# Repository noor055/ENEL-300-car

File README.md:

Link to Google drive: https://drive.google.com/drive/folders/1bgd8d79ywg4B1fOypwKYHgEbFJ_l1BKS?usp=sharing

Project Details:
Construct a RC car that will accomplish the following tasks:
1. Distance Sensing
2. Metal detecting
3. Design is more speed oriented

Contributers: Noor Sheikh, Ethan Lee, Youssef Salem, Ibrahim Khalid

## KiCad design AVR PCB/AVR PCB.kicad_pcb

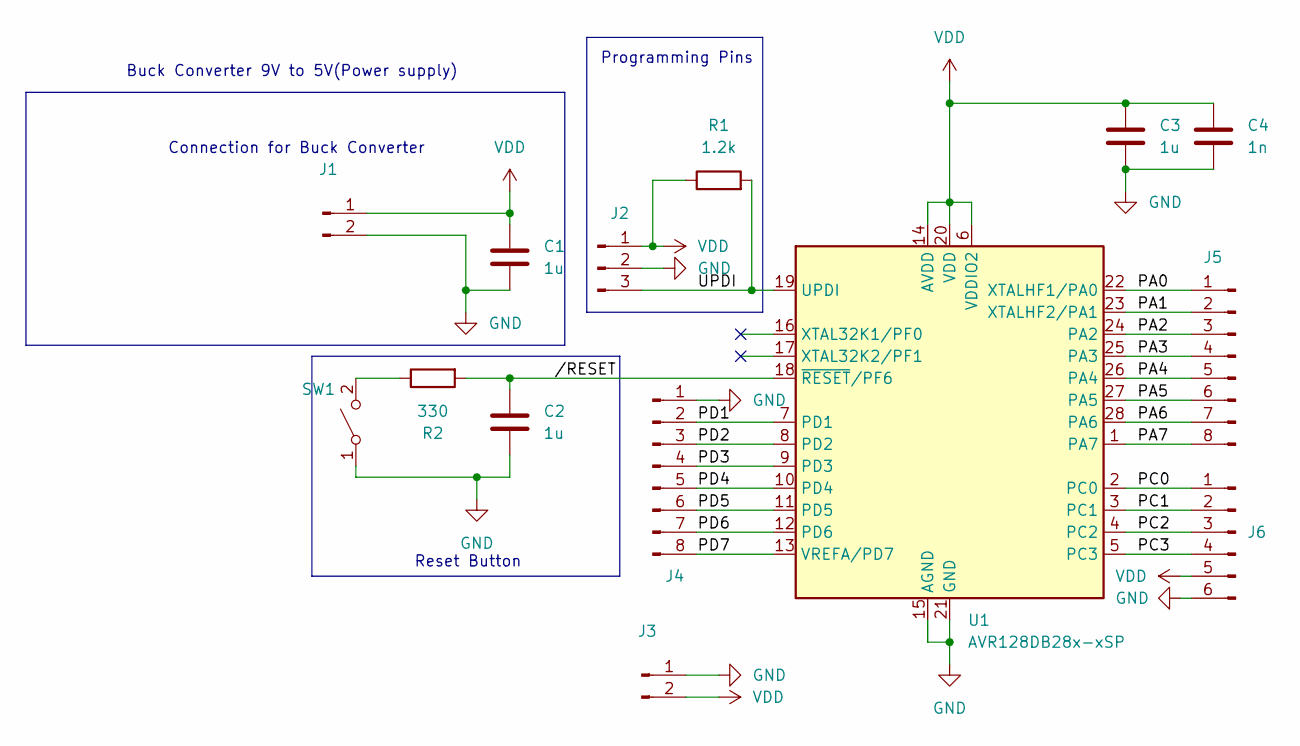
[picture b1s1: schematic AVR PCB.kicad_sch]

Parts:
C1, C2, C3: 1u; C_Disc_D7.5mm_W2.5mm_P5.00mm
C4: 1n; C_Disc_D7.5mm_W2.5mm_P5.00mm
J1: Conn_01x02_Pin; PinHeader_1x02_P2.54mm_Vertical
J2: Conn_01x03_Male; PinHeader_1x03_P2.54mm_Vertical
J3: Conn_01x02_Male; PinHeader_1x02_P2.54mm_Vertical
J4, J5: Conn_01x08_Male; PinHeader_1x08_P2.54mm_Vertical
J6: Conn_01x06_Male; PinHeader_1x06_P2.54mm_Vertical
R1: 1.2k; R_Axial_DIN0309_L9.0mm_D3.2mm_P12.70mm_Horizontal
R2: 330; R_Axial_DIN0309_L9.0mm_D3.2mm_P12.70mm_Horizontal
SW1: SW_SPST; SW_PUSH_6mm
U1: AVR128DB28x-xSP; DIP-28_W7.62mm

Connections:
/PA0: J5.1, U1.22 (XTALHF1/PA0)
/PA1: J5.2, U1.23 (XTALHF2/PA1)
/PA2: J5.3, U1.24 (PA2)
/PA3: J5.4, U1.25 (PA3)
/PA4: J5.5, U1.26 (PA4)
/PA5: J5.6, U1.27 (PA5)
/PA6: J5.7, U1.28 (PA6)
/PA7: J5.8, U1.1 (PA7)
/PC0: J6.1, U1.2 (PC0)
/PC1: J6.2, U1.3 (PC1)
/PC2: J6.3, U1.4 (PC2)
/PC3: J6.4, U1.5 (PC3)
/PD1: J4.2, U1.7 (PD1)
/PD2: J4.3, U1.8 (PD2)
/PD3: J4.4, U1.9 (PD3)
/PD4: J4.5, U1.10 (PD4)
/PD5: J4.6, U1.11 (PD5)
/PD6: J4.7, U1.12 (PD6)
/PD7: J4.8, U1.13 (VREFA/PD7)
/UPDI: J2.3, R1.2, U1.19 (UPDI)
//RESET: C2.1, R2.2, U1.18 (~RESET/PF6)
GND: C1.2, C2.2, C3.2, C4.2, J1.2, J2.2, J3.1, J4.1, J6.6, SW1.1 (A), U1.15 (AGND), U1.21 (GND)
unnamed: R2.1, SW1.2 (B)
VDD: C1.1, C3.1, C4.1, J1.1, J2.1, J3.2, J6.5, R1.1, U1.6 (VDDIO2), U1.14 (AVDD), U1.20 (VDD)

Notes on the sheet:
Reset Button
Programming Pins
Connection for Buck Converter
Buck Converter 9V to 5V(Power supply)

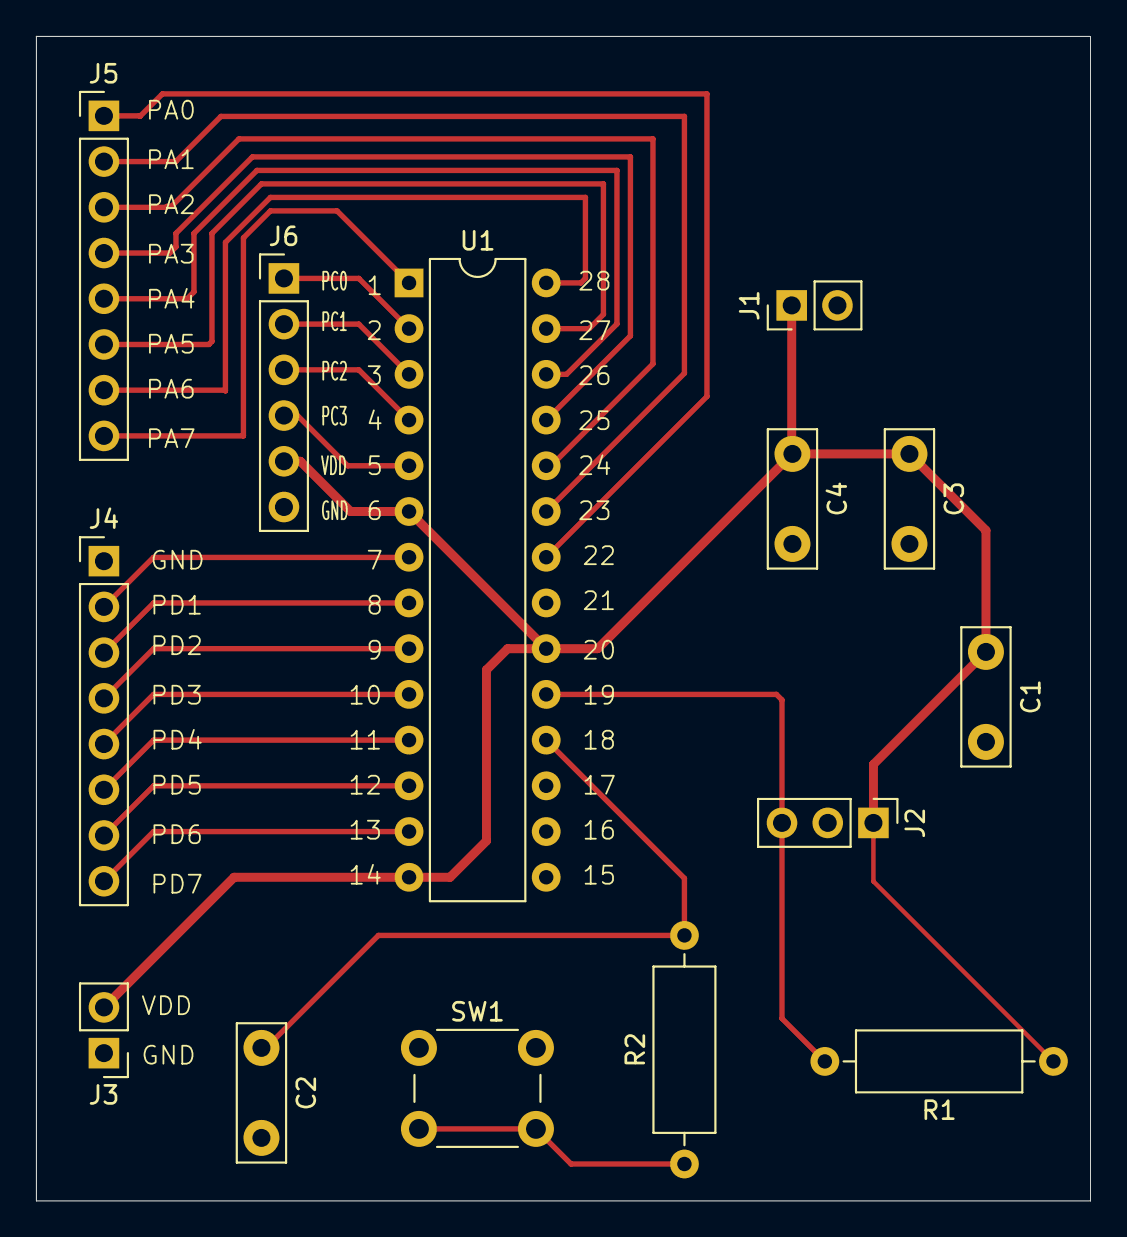
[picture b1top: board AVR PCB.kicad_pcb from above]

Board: 2 copper layers, 58.6 x 64.7 mm, 14 parts (0 on the bottom side), 24 nets.

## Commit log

2025-01-22 Create Link to Drive
2025-02-23 enel_5V_regulator
2025-02-23 metal_detector_pcb
2025-02-25 Add files via upload
    Version 2
2025-02-26 Delete buck_converter_enel300 directory
    PCB file fix
2025-03-11 working ultrasonic sensor code file
2025-04-20 Create rf.c
    Temporary somewhat functional rf controller/motor driver code.
2025-04-20 Add files via upload
    Untested metal detector with measuring threshold voltage to start
2025-04-24 Final project code
2025-04-24 Update main.c
    Added couple comments
2025-04-24 Update metaldetector.c
    added comment
